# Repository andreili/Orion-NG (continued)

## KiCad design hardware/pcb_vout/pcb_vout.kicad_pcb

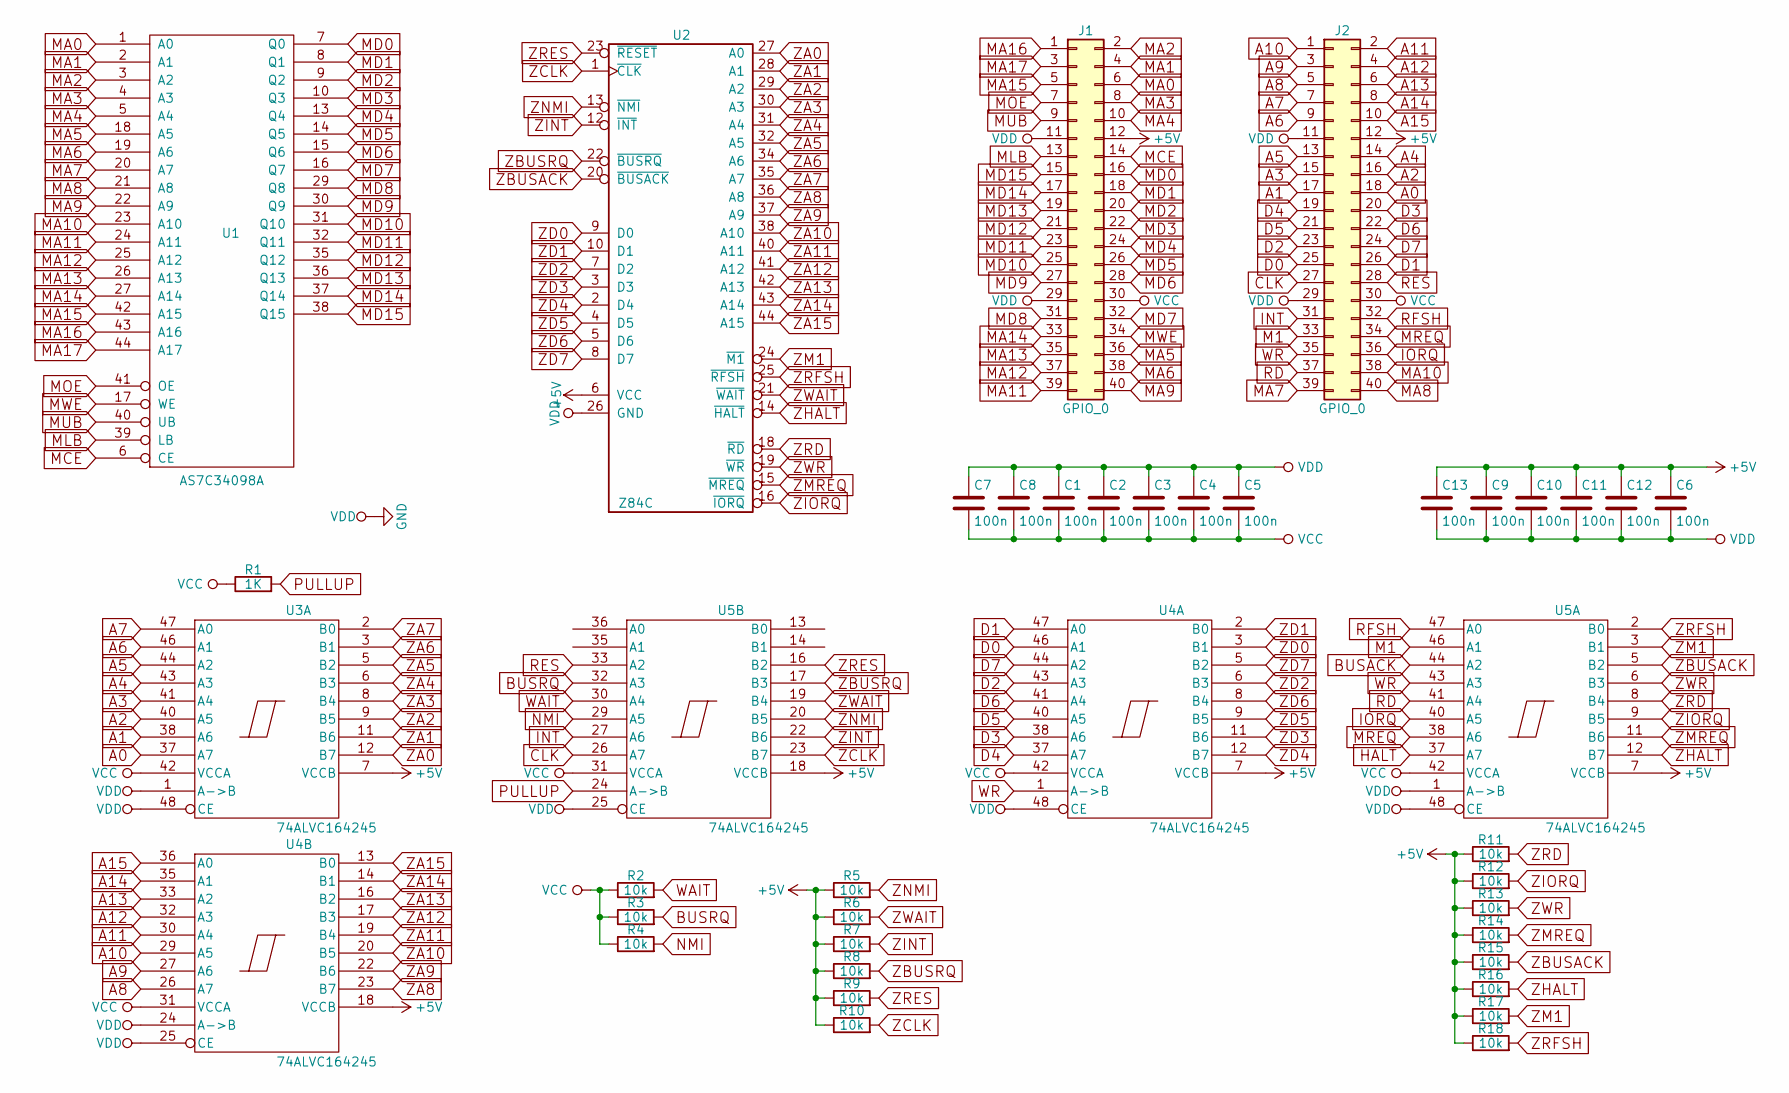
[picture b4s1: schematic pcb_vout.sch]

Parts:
C1, C2, C3, C4, C5, C6, C7, C8, C9, C10, C11, C12, C13: 100n; C_0805
J1, J2: GPIO_0; Socket_Strip_Straight_2x20_Pitch2.54mm
R1: 1K; R_0805
R2, R3, R4, R5, R6, R7, R8, R9, R10, R11, R12, R13, R14, R15, R16, R17, R18: 10k; R_0805
U1: AS7C34098A; TSOPII-44_10.16x18.5mm-Pitch0.8mm
U2: Z84C; LQFP-44_10x10mm_Pitch0.8mm
U3, U4, U5: 74ALVC164245; SSOP-48_7.5x15.9mm_Pitch0.635mm

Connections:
+5V: C6.1, C9.1, C10.1, C11.1, C12.1, C13.1, J1.12, J2.12, R5.1, R6.1, R7.1, R8.1, R9.1, R10.1, R11.1, R12.1, R13.1, R14.1, R15.1, R16.1, R17.1, R18.1, U2.6 (VCC), U3.7 (VCCB), U4.7 (VCCB), U4.18 (VCCB), U5.7 (VCCB), U5.18 (VCCB)
A0: J2.18, U3.37 (A7)
A1: J2.17, U3.38 (A6)
A2: J2.16, U3.40 (A5)
A3: J2.15, U3.41 (A4)
A4: J2.14, U3.43 (A3)
A5: J2.13, U3.44 (A2)
A6: J2.9, U3.46 (A1)
A7: J2.7, U3.47 (A0)
A8: J2.5, U4.26 (A7)
A9: J2.3, U4.27 (A6)
A10: J2.1, U4.29 (A5)
A11: J2.2, U4.30 (A4)
A12: J2.4, U4.32 (A3)
A13: J2.6, U4.33 (A2)
A14: J2.8, U4.35 (A1)
A15: J2.10, U4.36 (A0)
BUSACK: U5.44 (A2)
BUSRQ: R3.2, U5.32 (A3)
CLK: J2.27, U5.26 (A7)
D0: J2.25, U4.46 (A1)
D1: J2.26, U4.47 (A0)
D2: J2.23, U4.43 (A3)
D3: J2.20, U4.38 (A6)
D4: J2.19, U4.37 (A7)
D5: J2.21, U4.40 (A5)
D6: J2.22, U4.41 (A4)
D7: J2.24, U4.44 (A2)
GND: C1.1, C2.1, C3.1, C4.1, C5.1, C6.2, C7.1, C8.1, C9.2, C10.2, C11.2, C12.2, C13.2, J1.11, J1.29, J2.11, J2.29, U1.12 (GND), U1.34 (GND), U2.26 (GND), U3.1 (A->B), U3.4 (VDD), U3.10 (VDD), U3.15 (VDD), U3.21 (VDD), U3.28 (VDD), U3.34 (VDD), U3.39 (VDD), U3.45 (VDD), U3.48 (CE), U4.4 (VDD), U4.10 (VDD), U4.15 (VDD), U4.21 (VDD), U4.24 (A->B), U4.25 (CE), U4.28 (VDD), U4.34 (VDD), U4.39 (VDD), U4.45 (VDD), U4.48 (CE), U5.1 (A->B), U5.4 (VDD), U5.10 (VDD), U5.15 (VDD), U5.21 (VDD), U5.25 (CE), U5.28 (VDD), U5.34 (VDD), U5.39 (VDD), U5.45 (VDD), U5.48 (CE)
HALT: U5.37 (A7)
INT: J2.31, U5.27 (A6)
IORQ: J2.36, U5.40 (A5)
M1: J2.33, U5.46 (A1)
MA0: J1.6, U1.1 (A0)
MA1: J1.4, U1.2 (A1)
MA2: J1.2, U1.3 (A2)
MA3: J1.8, U1.4 (A3)
MA4: J1.10, U1.5 (A4)
MA5: J1.36, U1.18 (A5)
MA6: J1.38, U1.19 (A6)
MA7: J2.39, U1.20 (A7)
MA8: J2.40, U1.21 (A8)
MA9: J1.40, U1.22 (A9)
MA10: J2.38, U1.23 (A10)
MA11: J1.39, U1.24 (A11)
MA12: J1.37, U1.25 (A12)
MA13: J1.35, U1.26 (A13)
MA14: J1.33, U1.27 (A14)
MA15: J1.5, U1.42 (A15)
MA16: J1.1, U1.43 (A16)
MA17: J1.3, U1.44 (A17)
MCE: J1.14, U1.6 (CE)
MD0: J1.16, U1.7 (Q0)
MD1: J1.18, U1.8 (Q1)
MD2: J1.20, U1.9 (Q2)
MD3: J1.22, U1.10 (Q3)
MD4: J1.24, U1.13 (Q4)
MD5: J1.26, U1.14 (Q5)
MD6: J1.28, U1.15 (Q6)
MD7: J1.32, U1.16 (Q7)
MD8: J1.31, U1.29 (Q8)
MD9: J1.27, U1.30 (Q9)
MD10: J1.25, U1.31 (Q10)
MD11: J1.23, U1.32 (Q11)
MD12: J1.21, U1.35 (Q12)
MD13: J1.19, U1.36 (Q13)
MD14: J1.17, U1.37 (Q14)
MD15: J1.15, U1.38 (Q15)
MLB: J1.13, U1.39 (LB)
MOE: J1.7, U1.41 (OE)
MREQ: J2.34, U5.38 (A6)
MUB: J1.9, U1.40 (UB)
MWE: J1.34, U1.17 (WE)
NMI: R4.2, U5.29 (A5)
PULLUP: R1.2, U5.24 (A->B)
RD: J2.37, U5.41 (A4)
RES: J2.28, U5.33 (A2)
RFSH: J2.32, U5.47 (A0)
VCC: C1.2, C2.2, C3.2, C4.2, C5.2, C7.2, C8.2, J1.30, J2.30, R1.1, R2.1, R3.1, R4.1, U1.11 (VCC), U1.33 (VCC), U3.42 (VCCA), U4.31 (VCCA), U4.42 (VCCA), U5.31 (VCCA), U5.42 (VCCA)
WAIT: R2.2, U5.30 (A4)
WR: J2.35, U4.1 (A->B), U5.43 (A3)
ZA0: U2.27 (A0), U3.12 (B7)
ZA1: U2.28 (A1), U3.11 (B6)
ZA2: U2.29 (A2), U3.9 (B5)
ZA3: U2.30 (A3), U3.8 (B4)
ZA4: U2.31 (A4), U3.6 (B3)
ZA5: U2.32 (A5), U3.5 (B2)
ZA6: U2.34 (A6), U3.3 (B1)
ZA7: U2.35 (A7), U3.2 (B0)
ZA8: U2.36 (A8), U4.23 (B7)
ZA9: U2.37 (A9), U4.22 (B6)
ZA10: U2.38 (A10), U4.20 (B5)
ZA11: U2.40 (A11), U4.19 (B4)
ZA12: U2.41 (A12), U4.17 (B3)
ZA13: U2.42 (A13), U4.16 (B2)
ZA14: U2.43 (A14), U4.14 (B1)
ZA15: U2.44 (A15), U4.13 (B0)
ZBUSACK: R15.2, U2.20 (~BUSACK~), U5.5 (B2)
ZBUSRQ: R8.2, U2.22 (~BUSRQ~), U5.17 (B3)
ZCLK: R10.2, U2.1 (~CLK~), U5.23 (B7)
ZD0: U2.9 (D0), U4.3 (B1)
ZD1: U2.10 (D1), U4.2 (B0)
ZD2: U2.7 (D2), U4.6 (B3)
ZD3: U2.3 (D3), U4.11 (B6)
ZD4: U2.2 (D4), U4.12 (B7)
ZD5: U2.4 (D5), U4.9 (B5)
ZD6: U2.5 (D6), U4.8 (B4)
ZD7: U2.8 (D7), U4.5 (B2)
ZHALT: R16.2, U2.14 (~HALT~), U5.12 (B7)
ZINT: R7.2, U2.12 (~INT~), U5.22 (B6)
ZIORQ: R12.2, U2.16 (~IORQ~), U5.9 (B5)
ZM1: R17.2, U2.24 (~M1~), U5.3 (B1)
ZMREQ: R14.2, U2.15 (~MREQ~), U5.11 (B6)
ZNMI: R5.2, U2.13 (~NMI~), U5.20 (B5)
ZRD: R11.2, U2.18 (~RD~), U5.8 (B4)
ZRES: R9.2, U2.23 (~RESET~), U5.16 (B2)
ZRFSH: R18.2, U2.25 (~RFSH~), U5.2 (B0)
ZWAIT: R6.2, U2.21 (~WAIT~), U5.19 (B4)
ZWR: R13.2, U2.19 (~WR~), U5.6 (B3)

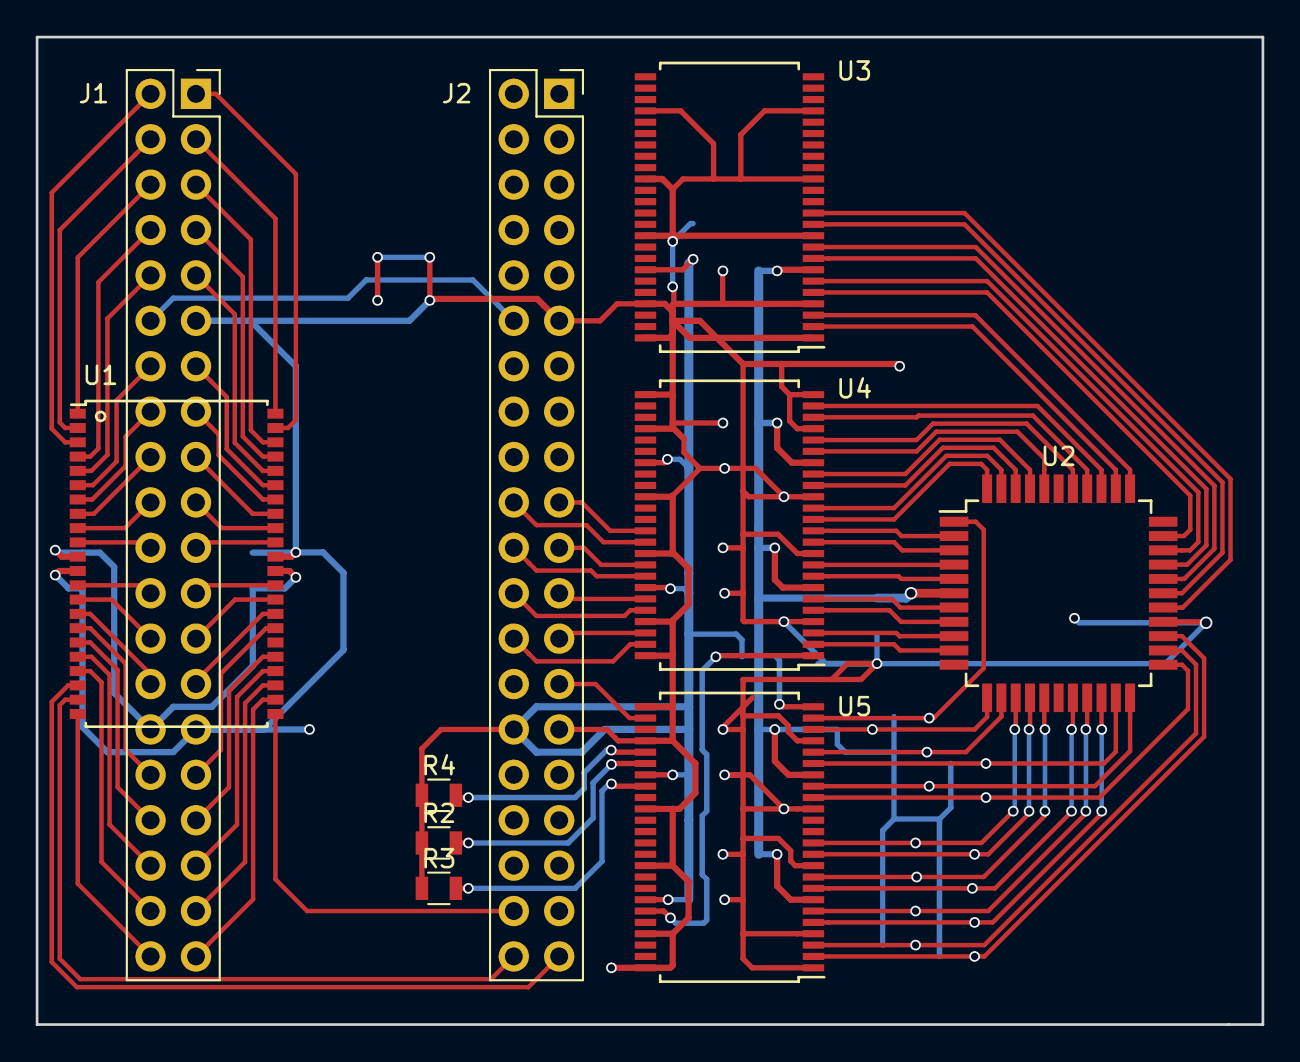
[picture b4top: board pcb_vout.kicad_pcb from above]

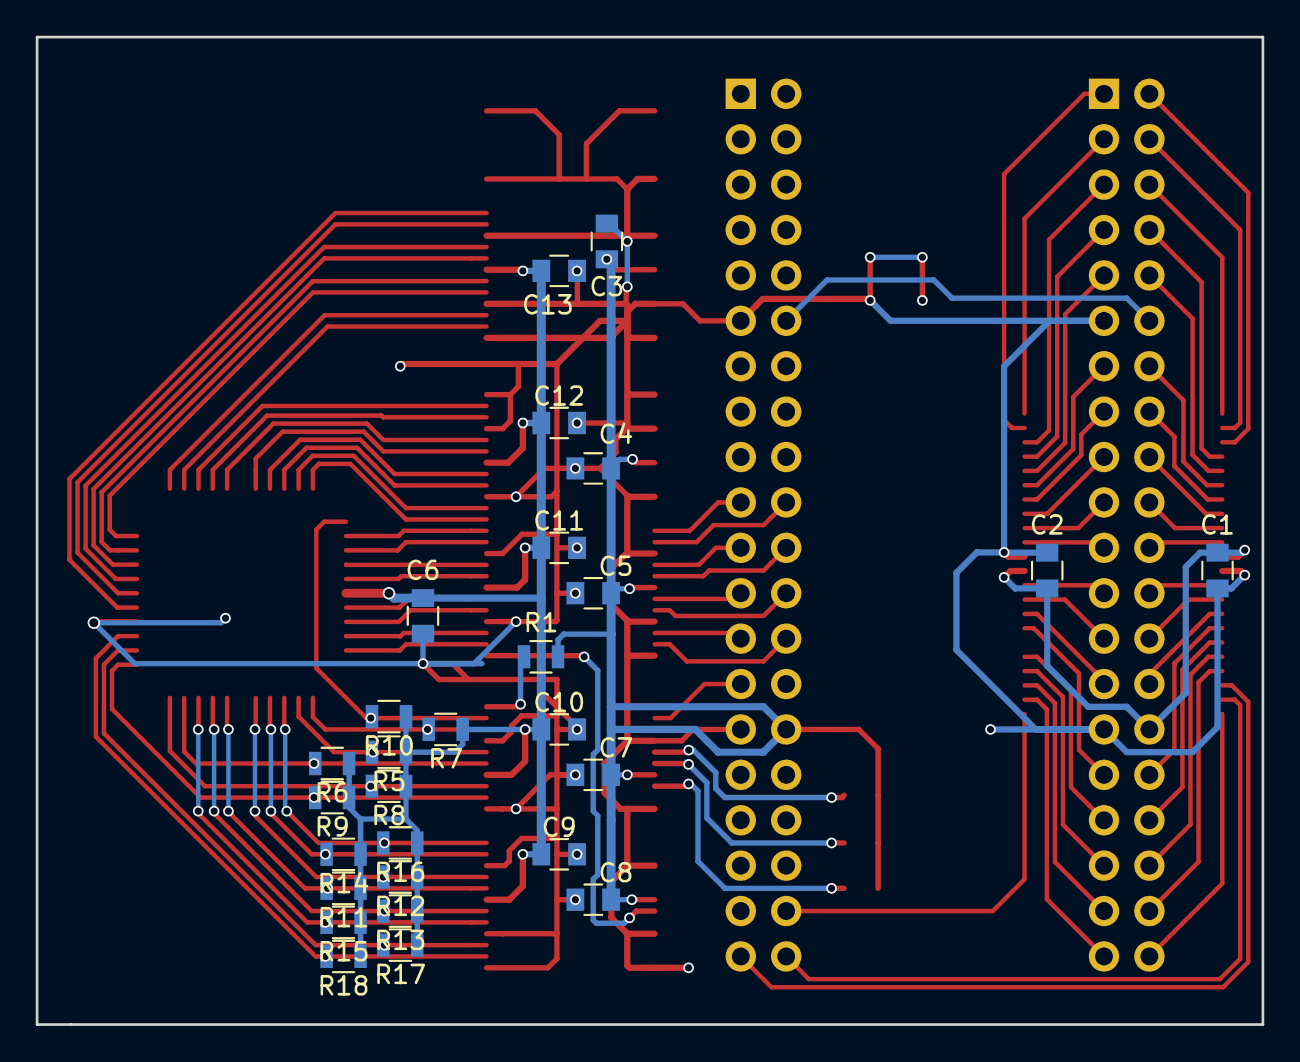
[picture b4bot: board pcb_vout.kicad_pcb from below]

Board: 2 copper layers, 68.6 x 55.2 mm, 38 parts (28 on the bottom side), 117 nets.

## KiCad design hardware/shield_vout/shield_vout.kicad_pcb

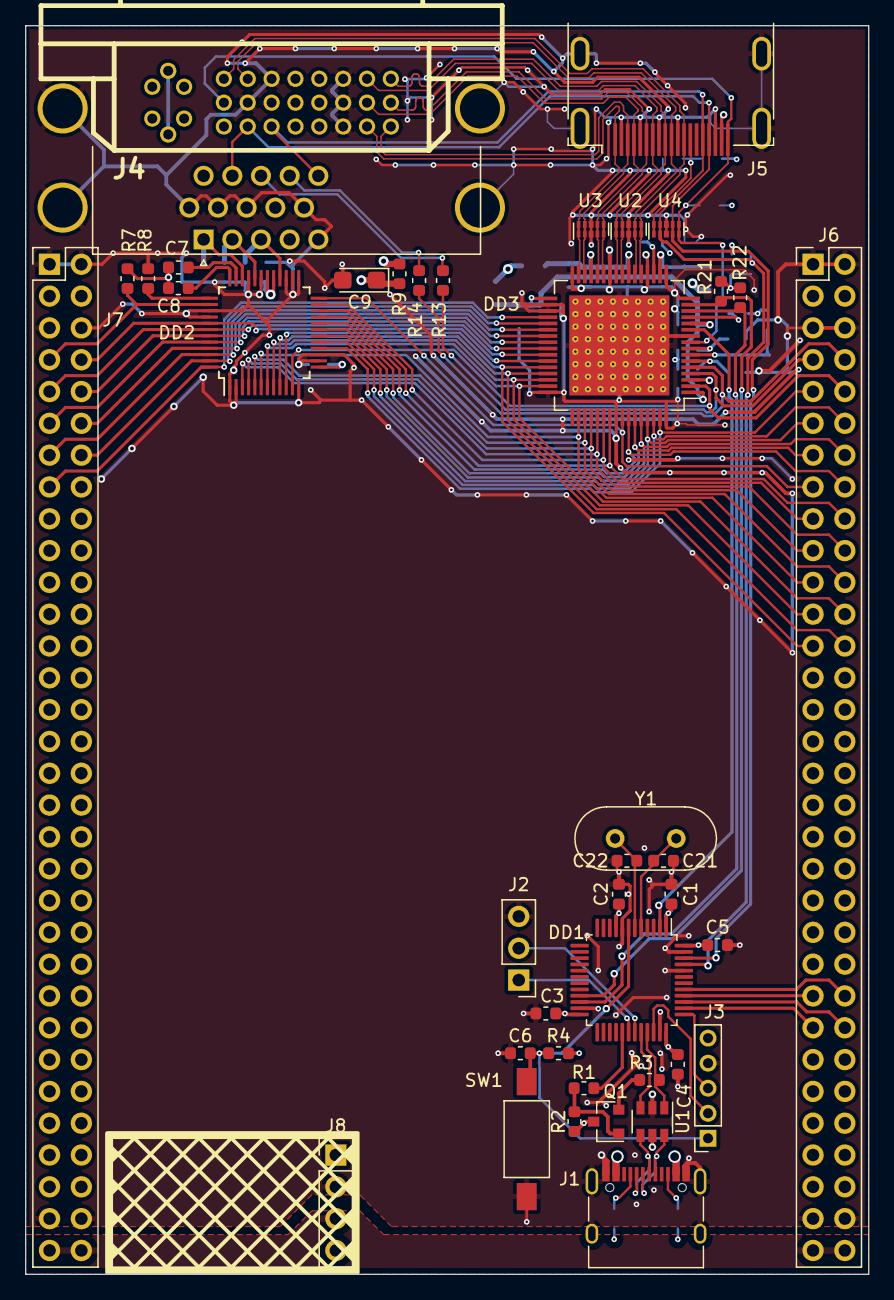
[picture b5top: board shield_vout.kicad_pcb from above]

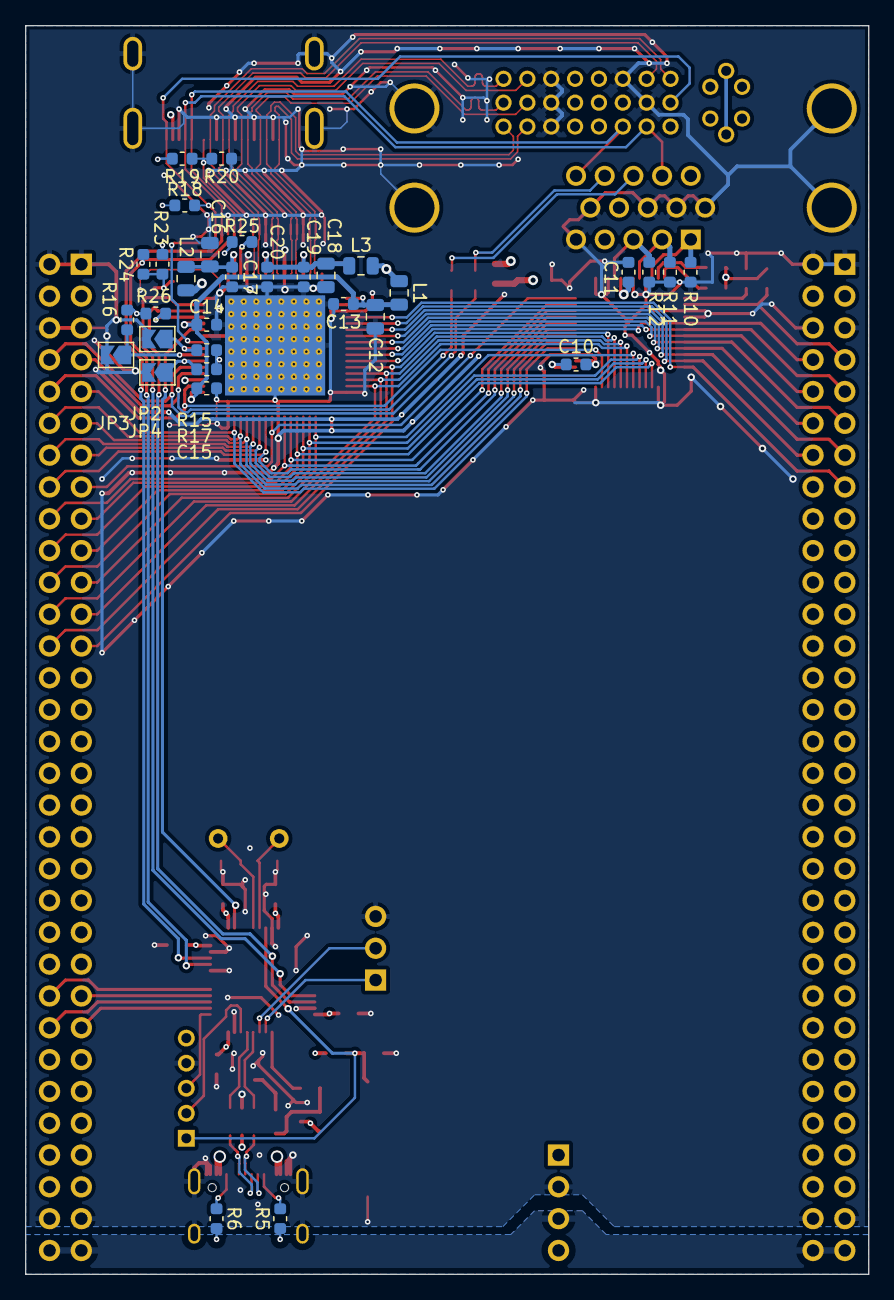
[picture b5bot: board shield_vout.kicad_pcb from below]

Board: 4 copper layers, 67.3 x 99.7 mm, 72 parts (32 on the bottom side), 84 nets.

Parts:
C1, C2, C3, C4, C5, C7, C8, C10, C11, C21, C22: 100n; C_0603_1608Metric
C6: 1u; C_0603_1608Metric
C9: 10u; CP_EIA-3216-18_Kemet-A
C12, C16, C18: 10uF; C_0805_2012Metric
C13, C14, C15, C17, C19, C20: 10n; C_0603_1608Metric
DD1: STM32F103CBTx; LQFP-48_7x7mm_P0.5mm
DD2: ADV7123; TQFP-48_7x7mm_P0.5mm
DD3: TFP410PAP; HTQFP-64-1EP_10x10mm_P0.5mm_EP8x8mm_Mask4.4x4.4mm_ThermalVi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
J1: USB; USB_C_Receptacle_XKB_U262-16XN-4BVC11
J2: UART; PinHeader_1x03_P2.54mm_Vertical
J3: SWD; PinSocket_1x05_P2.00mm_Vertical
J4: DVI_VGA; dvi_vga
J5: HDMI_A; HDMI_A_Amphenol
J6: U7; PinHeader_2x32_P2.54mm_Vertical
J7: U8; PinHeader_2x32_P2.54mm_Vertical
J8: ST_DN; PinHeader_1x04_P2.54mm_Vertical
JP2: A0; SolderJumper-2_P1.3mm_Open_TrianglePad1.0x1.5mm
JP3: A1; SolderJumper-2_P1.3mm_Open_TrianglePad1.0x1.5mm
JP4: A2; SolderJumper-2_P1.3mm_Open_TrianglePad1.0x1.5mm
L1, L2, L3: 10uH; L_0805_2012Metric
Q1: BC847; SOT-23
R1, R3, R7, R8, R18: 1k; R_0603_1608Metric
R2, R4: 10k; R_0603_1608Metric
R5, R6: 5k1; R_0603_1608Metric
R9: 0; R_0603_1608Metric
R10, R11, R12: 75; R_0603_1608Metric
R13, R14: 47; R_0603_1608Metric
R15, R16, R17, R20, R21, R22, R23, R24, R26: 2k; R_0603_1608Metric
R19: dnp; R_0603_1608Metric
R25: 510; R_0603_1608Metric
SW1: RESET; SW_SPST_FSMSM
U1: USBLC6-2SC6; SOT-23-6
U2, U3, U4: RCLAMP0524; USON-10_2.5x1.0mm_P0.5mm
Y1: 8MHz; Crystal_HC49-U_Vertical

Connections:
+3V3: C1.1, C2.1, C3.1, C4.1, C5.1, DD1.1 (VBAT), DD1.9 (VDDA), DD1.24 (VDD), DD1.36 (VDD), DD1.48 (VDD), DD3.3 (VREF), J6.3, J6.4, J7.3, J7.4, J8.1, L1.1, L2.1, L3.1, Q1.3 (C), R2.2, R4.2, R9.2, R15.2, R16.2, R17.2, R18.2, R19.2, R21.2, R22.2, R23.2, R24.2, R25.2, R26.2
+5V: J1.A4 (VBUS), J1.A9 (VBUS), J1.B4 (VBUS), J1.B9 (VBUS), J4.14, J4.v9, J5.18 (+5V), J6.63, J6.64, J7.63, J7.64, J8.3, U1.5 (VBUS)
/I2C1_SCL: DD1.45 (PB8), J4.6, J4.v15, J5.15 (SCL), R24.1, U4.2, U4.9
/I2C2_SCL: DD1.21 (PB10), DD3.15 (BSEL/SCL), R21.1
/INT: DD1.2 (PC13), DD3.11 (MSEN/PO1)
/MCU/USB+: J1.A6 (D+), J1.B6 (D+), U1.6 (I/O1)
/MCU/USB-: J1.A7 (D-), J1.B7 (D-), U1.4 (I/O2)
/NSS: DD1.17 (PA7), J6.49
/SCK: DD1.16 (PA6), J6.50
/SDA: DD1.22 (PB11), DD3.14 (DSEL/SDA), R22.1
/SI: DD1.14 (PA4), J6.48
/SO: DD1.15 (PA5), J6.47
/VGA_SDA: DD1.46 (PB9), J4.7, J4.v12, J5.16 (SDA), R23.1, U4.4, U4.7
/Video Output/+3V3_VGA: C7.2, C8.2, C9.1, C10.1, C11.1, DD2.13 (VAA), DD2.29 (VAA), DD2.30 (VAA), R7.1, R9.1
/Video Output/A0: DD3.8 (CTL1/A1/DK1), JP2.1 (A), R15.1
/Video Output/A1: DD3.7 (CTL2/A2/DK2), JP3.1 (A), R16.1
/Video Output/A2: DD3.6 (CTL3/A3/DK3), JP4.1 (A), R17.1
/Video Output/B0: DD2.16 (B2), DD3.63 (DATA0), J6.9
/Video Output/B1: DD2.17 (B3), DD3.62 (DATA1), J6.12
/Video Output/B2: DD2.18 (B4), DD3.61 (DATA2), J6.11
/Video Output/B3: DD2.19 (B5), DD3.60 (DATA3), J6.14
/Video Output/B4: DD2.20 (B6), DD3.59 (DATA4), J6.13
/Video Output/B5: DD2.21 (B7), DD3.58 (DATA5), J6.16
/Video Output/B6: DD2.22 (B8), DD3.55 (DATA6), J6.18
/Video Output/B7: DD2.23 (B9), DD3.54 (DATA7), J6.17
/Video Output/BL: DD2.11 (~BLANK), DD3.2 (DE), J6.10
/Video Output/B_2: DD2.28 (IOB), J4.v3, R12.2
/Video Output/CEC: J5.13 (CEC), R19.1, R20.2, U4.1, U4.10
/Video Output/G0: DD2.3 (G2), DD3.53 (DATA8), J6.20
/Video Output/G1: DD2.4 (G3), DD3.52 (DATA9), J6.19
/Video Output/G2: DD2.5 (G4), DD3.51 (DATA10), J6.22
/Video Output/G3: DD2.6 (G5), DD3.50 (DATA11), J6.21
/Video Output/G4: DD2.7 (G6), DD3.47 (DATA12), J6.24
/Video Output/G5: DD2.8 (G7), DD3.46 (DATA13), J6.23
/Video Output/G6: DD2.9 (F8), DD3.45 (DATA14), J6.26
/Video Output/G7: DD2.10 (G9), DD3.44 (DATA15), J6.25
/Video Output/G_2: DD2.32 (IOG), J4.v2, R11.2
/Video Output/HPD: DD3.9 (EDGE/HTPLG), J4.16, J5.19 (HPD), R18.1, U4.5, U4.6
/Video Output/HS: DD3.4 (HSYNC), J6.7, R13.2
/Video Output/PCLK: DD2.24 (CLOCK), DD3.57 (IDCK+), J6.15
/Video Output/PSAVE: DD2.38 (~PSAVE), J7.7, R7.2
/Video Output/R0: DD2.41 (R2), DD3.43 (DATA16), J7.8
/Video Output/R1: DD2.42 (R3), DD3.42 (DATA17), J7.9
/Video Output/R2: DD2.43 (R4), DD3.41 (DATA18), J7.10
/Video Output/R3: DD2.44 (R5), DD3.40 (DATA19), J7.11
/Video Output/R4: DD2.45 (R6), DD3.39 (DATA20), J7.12
/Video Output/R5: DD2.46 (R7), DD3.38 (DATA21), J7.13
/Video Output/R6: DD2.47 (R8), DD3.37 (DATA22), J7.14
/Video Output/R7: DD2.48 (R9), DD3.36 (DATA23), J7.15
/Video Output/R_2: DD2.34 (IOR), J4.v1, R10.2
/Video Output/TX0+: DD3.25 (TX0+), J4.18, J5.7 (D0+), U2.1, U2.10
/Video Output/TX0-: DD3.24 (TX0-), J4.17, J5.9 (D0-), U2.2, U2.9
/Video Output/TX1+: DD3.28 (TX1+), J4.10, J5.4 (D1+), U3.4, U3.7
/Video Output/TX1-: DD3.27 (TX1-), J4.9, J5.6 (D1-), U3.5, U3.6
/Video Output/TX2+: DD3.31 (TX2+), J4.2, J5.1 (D2+), U3.1, U3.10
/Video Output/TX2-: DD3.30 (TX2-), J4.1, J5.3 (D2-), U3.2, U3.9
/Video Output/TXC+: DD3.22 (TXC+), J4.23, J5.10 (CK+), U2.4, U2.7
/Video Output/TXC-: DD3.21 (TXC-), J4.24, J5.12 (CK-), U2.5, U2.6
/Video Output/VS: DD3.5 (VSYNC), J6.8, R14.2
AVDD: C18.1, C19.1, C20.1, DD3.23 (TVDD), DD3.29 (TVDD), L3.2
D+: DD1.33 (PA12), R3.2, U1.1 (I/O1)
D-: DD1.32 (PA11), U1.3 (I/O2)
DVDD: C12.1, C13.1, C14.1, C15.1, DD3.1 (DVDD), DD3.12 (DVDD), DD3.33 (DVDD), L1.2
GND: C1.2, C2.2, C3.2, C4.2, C5.2, C6.2, C9.2, C10.2, C11.2, C12.2, C13.2, C14.2, C15.2, C16.2, C17.2, C18.2, C19.2, C20.2, C21.2, C22.2, DD1.8 (VSSA), DD1.23 (VSS), DD1.35 (VSS), DD1.44 (BOOT0), DD1.47 (VSS), DD2.1 (G0), DD2.2 (G1), DD2.12 (~SYNC), DD2.14 (B0), DD2.15 (B1), DD2.25 (GND), DD2.26 (GND), DD2.27 (~IOB), DD2.31 (~IOG), DD2.33 (~IOR), DD2.39 (R0), DD2.40 (R1), DD3.10 (~PD), DD3.16 (DGND), DD3.17 (PGND), DD3.20 (TGND), DD3.26 (TGND), DD3.32 (TGND), DD3.34 (RESERVED), DD3.35 (DKEN), DD3.48 (DGND), DD3.56 (IDCK-), DD3.64 (DGND), DD3.65 (EP), J1.A1 (GND), J1.A12 (GND), J1.B1 (GND), J1.B12 (GND), J1.S1 (SHIELD), J2.3, J3.4, J4.3, J4.11, J4.15, J4.19, J4.22, J4.SH, J4.v5, J4.v6, J4.v7, J4.v8, J4.v10, J5.2 (D2S), J5.5 (D1S), J5.8 (D0S), J5.11 (CKS), J5.17 (GND), J5.SH, J6.1, J6.2, J6.5, J6.6, J6.61, J6.62, J7.1, J7.2, J7.5, J7.6, J7.61, J7.62, J8.2, JP2.2 (B), JP3.2 (B), JP4.2 (B), R5.1, R6.1, R8.1, R10.1, R11.1, R12.1, R20.1, SW1.2, U1.2 (GND), U2.3 (GND), U2.8 (GND), U3.3 (GND), U3.8 (GND), U4.3 (GND), U4.8 (GND)
NRST: C6.1, DD1.7 (NRST), J3.1, R4.1, SW1.1
unnamed: C7.1, DD2.35 (COMP)
unnamed: C8.1, DD2.36 (VREF)
unnamed: DD2.37 (RSET), R8.2
unnamed: DD3.13 (ISEL/~RST), R26.1
unnamed: DD3.19 (TFADJ), R25.1
unnamed: J1.A5 (CC1), R5.2
unnamed: J1.B5 (CC2), R6.2
unnamed: J4.v13, R13.1
unnamed: J4.v14, R14.1
unnamed: Q1.1 (B), R1.2, R2.1
unnamed: Q1.2 (E), R3.1
OSC_IN: C21.1, DD1.5 (PD0), Y1.1
OSC_OUT: C22.1, DD1.6 (PD1), Y1.2
PVDD: C16.1, C17.1, DD3.18 (PVDD), L2.2
RX: DD1.31 (PA10), J2.2
SWCLK: DD1.37 (PA14), J3.3
SWDIO: DD1.34 (PA13), J3.2
TX: DD1.30 (PA9), J2.1
USB_EN: DD1.29 (PA8), R1.1

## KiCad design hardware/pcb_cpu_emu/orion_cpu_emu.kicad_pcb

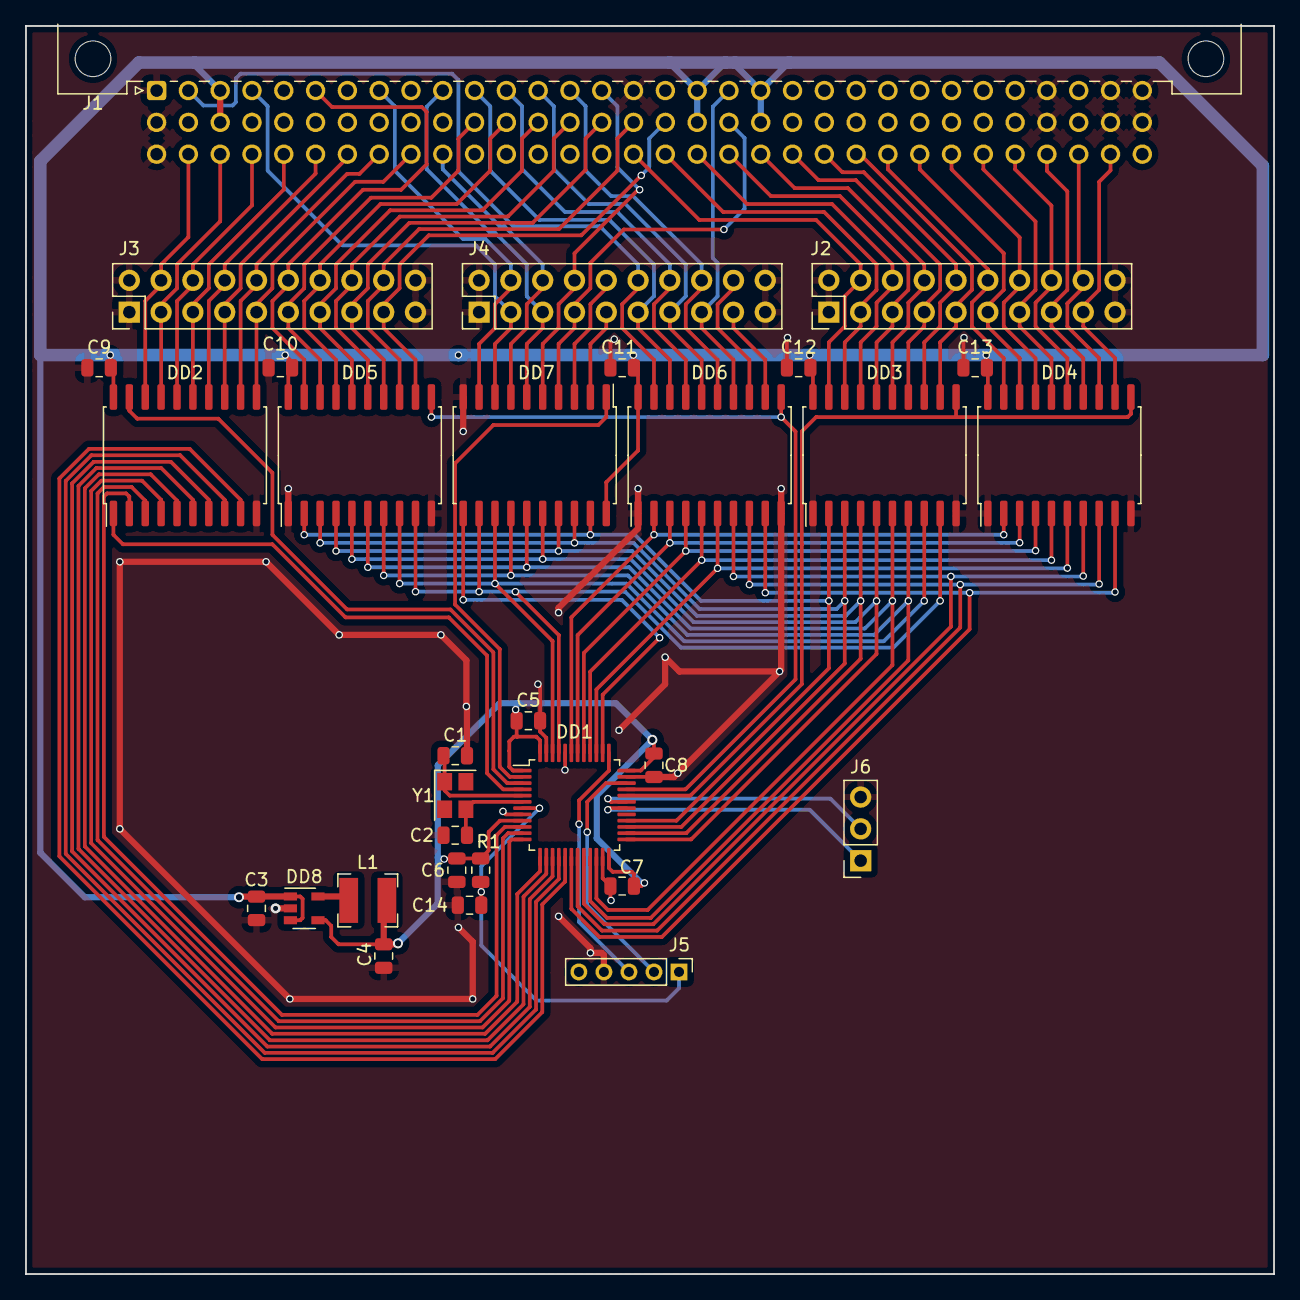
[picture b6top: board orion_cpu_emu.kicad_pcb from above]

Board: 2 copper layers, 99.7 x 99.7 mm, 31 parts (0 on the bottom side), 89 nets.

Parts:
C1, C2: 22pf; C_0805_2012Metric
C3, C4, C14: 4.7u; C_0805_2012Metric
C5, C6, C7, C8, C9, C10, C11, C12, C13: 100n; C_0805_2012Metric
DD1: STM32F103CBTx; LQFP-48_7x7mm_P0.5mm
DD2: AP6; SOIC-20W_7.5x12.8mm_P1.27mm
DD3, DD4, DD5, DD6, DD7: IR33; SOIC-20W_7.5x12.8mm_P1.27mm
DD8: LM3671MF; SOT-23-5
J1: C96ABC; DIN41612_C_3x32_Male_Horizontal_THT
J2, J3, J4: Conn_02x10_Odd_Even; PinHeader_2x10_P2.54mm_Vertical
J5: SWD; PinHeader_1x05_P2.00mm_Vertical
J6: UART; PinSocket_1x03_P2.54mm_Vertical
L1: 4,7uH; L_Bourns-SRN4018
R1: 1k; R_0805_2012Metric
Y1: 8MHz; Crystal_SMD_3225-4Pin_3.2x2.5mm

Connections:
+3V3: C4.1, C5.1, C6.1, C7.1, C8.1, DD1.1 (VBAT), DD1.9 (VDDA), DD1.24 (VDD), DD1.36 (VDD), DD1.48 (VDD), DD8.4 (FB), L1.2, R1.1
/A0: DD4.12 (7), J1.c31 (C31), J2.17
/A1: DD4.13 (6), J1.c30 (C30), J2.18
/A2: DD4.14 (5), J1.c29 (C29), J2.15
/A3: DD4.15 (4), J1.c28 (C28), J2.16
/A4: DD4.16 (3), J1.c27 (C27), J2.13
/A5: DD4.17 (2), J1.c26 (C26), J2.14
/A6: DD4.18 (1), J1.c25 (C25), J2.11
/A7: DD4.19 (0), J1.c24 (C24), J2.12
/A8: DD3.12 (7), J1.c23 (C23), J2.9
/A9: DD3.13 (6), J1.c22 (C22), J2.10
/A10: DD3.14 (5), J1.c21 (C21), J2.7
/A11: DD3.15 (4), J1.c20 (C20), J2.8
/A12: DD3.16 (3), J1.c19 (C19), J2.5
/A13: DD3.17 (2), J1.c18 (C18), J2.6
/A14: DD3.18 (1), J1.c17 (C17), J2.3
/A15: DD3.19 (0), J1.c16 (C16), J2.4
/AA0: DD6.13 (6), J4.18
/AA1: DD6.12 (7), J4.17
/AB0: DD7.2 (0), J4.9
/AB1: DD7.3 (1), J4.10
/D0: DD2.11 (B7), J1.c9 (C9), J3.9
/D1: DD2.12 (B6), J1.c8 (C8), J3.10
/D2: DD2.13 (B5), J1.c7 (C7), J3.7
/D3: DD2.14 (B4), J1.c6 (C6), J3.8
/D4: DD2.15 (B3), J1.c5 (C5), J3.5
/D5: DD2.16 (B2), J1.c4 (C4), J3.6
/D6: DD2.17 (B1), J1.c3 (C3), J3.3
/D7: DD2.18 (B0), J1.c2 (C2), J3.4
/FEND: DD7.4 (2), J1.b19 (B19), J4.7
/HOLD: DD7.5 (3), J1.a15 (A15), J4.8
/IORQ: DD6.18 (1), J1.a11 (A11), J4.11
/M1: DD5.19 (0), J1.a6 (A6), J3.12
/MA14: DD5.12 (7), J1.b17 (B17), J3.17
/MA15: DD5.13 (6), J1.b16 (B16), J3.18
/MA16: DD5.14 (5), J1.b15 (B15), J3.15
/MA17: DD5.15 (4), J1.b14 (B14), J3.16
/MA18: DD5.16 (3), J1.b13 (B13), J3.13
/MA19: DD5.17 (2), J1.b12 (B12), J3.14
/MA20: DD5.18 (1), J1.b11 (B11), J3.11
/MREQ: DD6.17 (2), J1.a12 (A12), J4.14
/RD: DD6.15 (4), J1.a14 (A14), J4.16
/RES: DD6.19 (0), J1.a2 (A2), J4.12
/RFSH: DD6.14 (5), J1.a19 (A19), J4.15
/WR: DD6.16 (3), J1.a13 (A13), J4.13
/~BLIO: DD7.6 (4), J1.a10 (A10), J4.5
/~BLRAM: DD7.9 (7), J1.a8 (A8), J4.4
/~INTA: DD7.8 (6), J1.a4 (A4), J4.3
/~WAIT: DD7.7 (5), J1.c10 (C10), J4.6
DDIR: DD1.4 (PC15), DD2.1 (A/B)
DOE: DD1.3 (PC14), DD2.19 (OE)
GND: C1.2, C2.2, C3.2, C4.2, C5.2, C6.2, C7.2, C8.2, C9.2, C10.2, C11.2, C12.2, C13.2, C14.2, DD1.8 (VSSA), DD1.23 (VSS), DD1.35 (VSS), DD1.44 (BOOT0), DD1.47 (VSS), DD2.10 (GND), DD3.1 (OE), DD3.10 (GND), DD4.1 (OE), DD4.10 (GND), DD5.1 (OE), DD5.10 (GND), DD6.1 (OE), DD6.10 (GND), DD7.10 (GND), DD8.2 (GND), J1.a1 (A1), J1.a16 (A16), J1.a29 (A29), J1.a31 (A31), J1.a32 (A32), J1.b1 (B1), J1.b29 (B29), J1.b31 (B31), J1.b32 (B32), J1.c1 (C1), J2.1, J2.2, J2.19, J2.20, J3.1, J3.2, J3.19, J3.20, J4.1, J4.2, J4.19, J4.20, J5.4, J6.3
LE0: DD1.32 (PA11), DD3.11 (LE), DD4.11 (LE)
LE1: DD1.33 (PA12), DD5.11 (LE), DD6.11 (LE)
LE2: DD1.38 (PA15), DD7.11 (LE)
NRST: C14.1, DD1.7 (NRST), J5.1, R1.2
unnamed: DD8.5 (SW), L1.1
OE2: DD1.2 (PC13), DD7.1 (OE)
OSC_IN: C1.1, DD1.5 (PD0), Y1.1
OSC_OUT: C2.1, DD1.6 (PD1), Y1.3
PA0: DD1.10 (PA0), DD2.2 (A0)
PA1: DD1.11 (PA1), DD2.3 (A1)
PA2: DD1.12 (PA2), DD2.4 (A2)
PA3: DD1.13 (PA3), DD2.5 (A3)
PA4: DD1.14 (PA4), DD2.6 (A4)
PA5: DD1.15 (PA5), DD2.7 (A5)
PA6: DD1.16 (PA6), DD2.8 (A6)
PA7: DD1.17 (PA7), DD2.9 (A7)
PB0: DD1.18 (PB0), DD4.9 (7), DD6.9 (7)
PB1: DD1.19 (PB1), DD4.8 (6), DD6.8 (6)
PB2: DD1.20 (PB2), DD4.7 (5), DD6.7 (5)
PB3: DD1.39 (PB3), DD4.6 (4), DD6.6 (4)
PB4: DD1.40 (PB4), DD4.5 (3), DD6.5 (3)
PB5: DD1.41 (PB5), DD4.4 (2), DD6.4 (2)
PB6: DD1.42 (PB6), DD4.3 (1), DD6.3 (1)
PB7: DD1.43 (PB7), DD4.2 (0), DD6.2 (0)
PB8: DD1.45 (PB8), DD3.9 (7), DD5.9 (7), DD7.12 (7)
PB9: DD1.46 (PB9), DD3.8 (6), DD5.8 (6), DD7.13 (6)
PB10: DD1.21 (PB10), DD3.7 (5), DD5.7 (5), DD7.14 (5)
PB11: DD1.22 (PB11), DD3.6 (4), DD5.6 (4), DD7.15 (4)
PB12: DD1.25 (PB12), DD3.5 (3), DD5.5 (3), DD7.16 (3)
PB13: DD1.26 (PB13), DD3.4 (2), DD5.4 (2), DD7.17 (2)
PB14: DD1.27 (PB14), DD3.3 (1), DD5.3 (1), DD7.18 (1)
PB15: DD1.28 (PB15), DD3.2 (0), DD5.2 (0), DD7.19 (0)
RX: DD1.31 (PA10), J6.2
SWCLK: DD1.37 (PA14), J5.3
SWDIO: DD1.34 (PA13), J5.2
TX: DD1.30 (PA9), J6.1
VCC: C3.1, C9.1, C10.1, C11.1, C12.1, C13.1, DD2.20 (VCC), DD3.20 (VCC), DD4.20 (VCC), DD5.20 (VCC), DD6.20 (VCC), DD7.20 (VCC), DD8.1 (Vin), DD8.3 (EN), J1.a3 (A3), J1.a18 (A18), J1.a20 (A20), J1.b3 (B3), J1.b18 (B18), J1.b20 (B20)
